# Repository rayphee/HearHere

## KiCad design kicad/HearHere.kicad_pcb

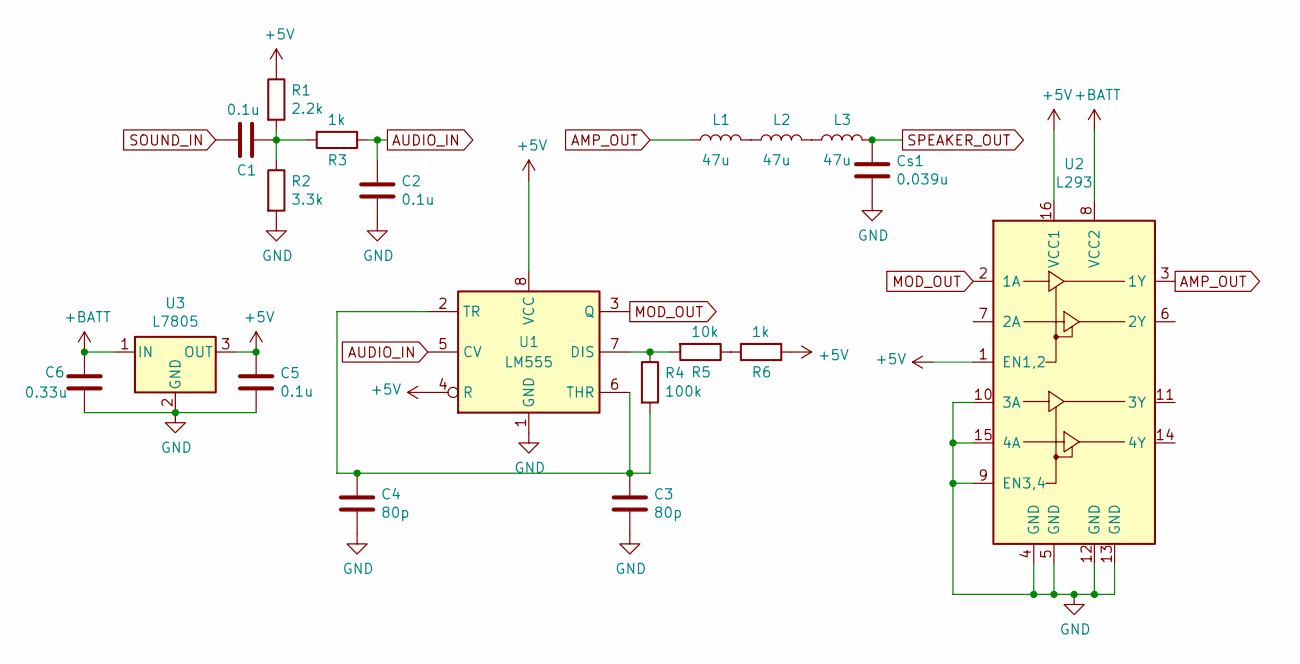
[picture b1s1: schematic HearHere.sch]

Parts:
C1, C2, C5: 0.1u; C_Axial_L3.8mm_D2.6mm_P7.50mm_Horizontal
C3, C4: 80p; C_Axial_L3.8mm_D2.6mm_P7.50mm_Horizontal
C6: 0.33u; C_Axial_L3.8mm_D2.6mm_P7.50mm_Horizontal
Cs1: 0.039u; C_Axial_L3.8mm_D2.6mm_P7.50mm_Horizontal
L1, L2, L3: 47u; L_Axial_L9.5mm_D4.0mm_P12.70mm_Horizontal_Fastron_SMCC
R1: 2.2k; R_Axial_DIN0309_L9.0mm_D3.2mm_P12.70mm_Horizontal
R2: 3.3k; R_Axial_DIN0309_L9.0mm_D3.2mm_P12.70mm_Horizontal
R3: 1k; R_Axial_DIN0411_L9.9mm_D3.6mm_P12.70mm_Horizontal
R4: 100k; R_Axial_DIN0411_L9.9mm_D3.6mm_P12.70mm_Horizontal
R5: 10k; R_Axial_DIN0309_L9.0mm_D3.2mm_P12.70mm_Horizontal
R6: 1k; R_Axial_DIN0309_L9.0mm_D3.2mm_P12.70mm_Horizontal
U1: LM555; DIP-8_W7.62mm_Socket
U2: L293; DIP-16_W7.62mm_Socket
U3: L7805; TO-220-3_Horizontal

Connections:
+5V: C5.1, R1.1, R6.1, U1.4 (R), U1.8 (VCC), U2.1 (EN1,2), U2.16 (VCC1), U3.3 (OUT)
+BATT: C6.1, U2.8 (VCC2), U3.1 (IN)
AMP_OUT: L1.1, U2.3 (1Y)
AUDIO_IN: C2.1, R3.1, U1.5 (CV)
GND: C2.2, C3.2, C4.2, C5.2, C6.2, Cs1.2, R2.2, U1.1 (GND), U2.4 (GND), U2.5 (GND), U2.9 (EN3,4), U2.10 (3A), U2.12 (GND), U2.13 (GND), U2.15 (4A), U3.2 (GND)
MOD_OUT: U1.3 (Q), U2.2 (1A)
unnamed: C1.1, R1.2, R2.1, R3.2
unnamed: C3.1, C4.1, R4.2, U1.2 (TR), U1.6 (THR)
unnamed: L1.2, L2.1
unnamed: L2.2, L3.1
unnamed: R4.1, R5.2, U1.7 (DIS)
unnamed: R5.1, R6.2
SOUND_IN: C1.2
SPEAKER_OUT: Cs1.1, L3.2

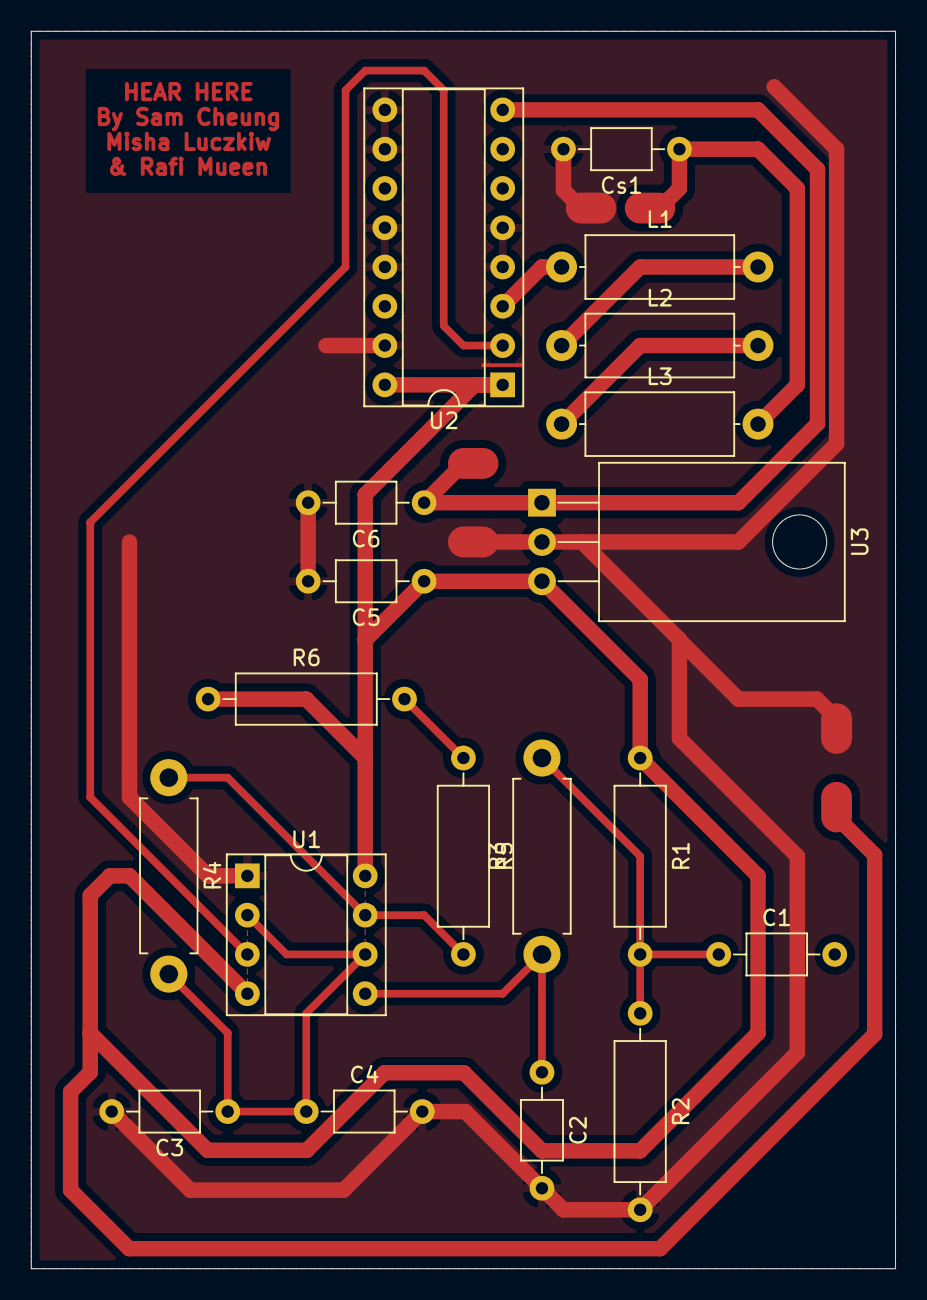
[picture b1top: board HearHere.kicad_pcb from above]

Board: 2 copper layers, 55.9 x 80.0 mm, 19 parts (0 on the bottom side), 13 nets.

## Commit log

2019-04-28 "Added some more initial work"
2019-05-04 Adjusted Project Poster
